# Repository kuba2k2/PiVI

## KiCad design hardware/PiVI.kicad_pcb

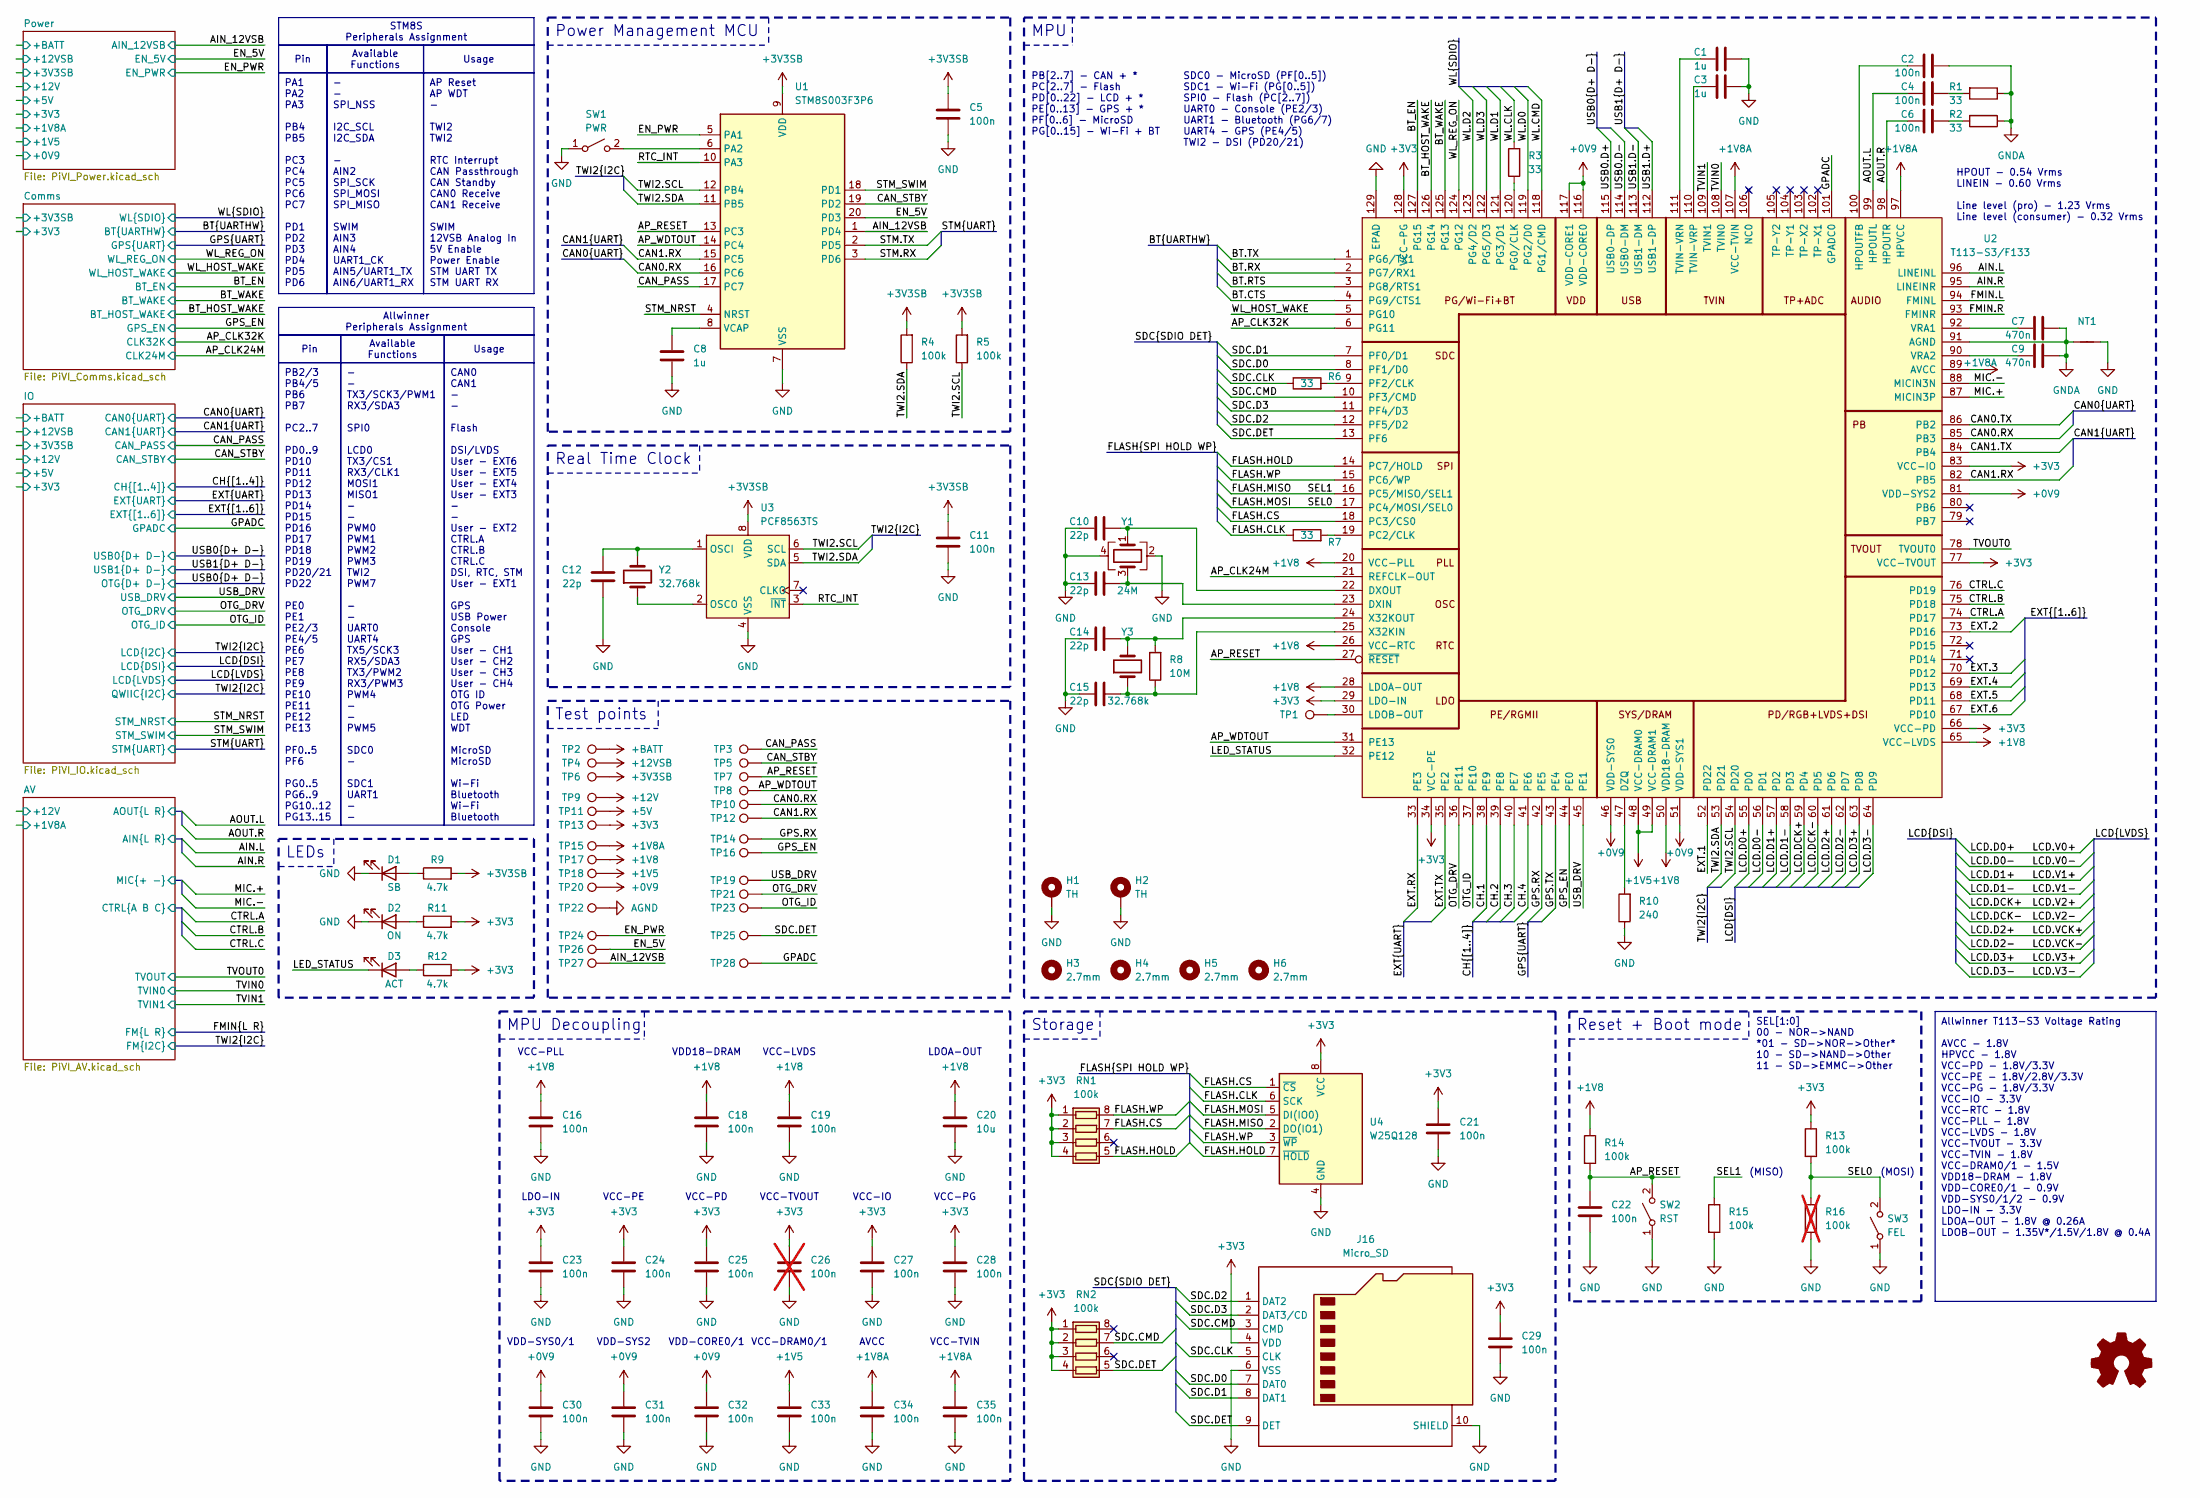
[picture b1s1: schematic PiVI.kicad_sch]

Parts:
C1, C3, C8: 1u; C_0603_1608Metric; MPN C29936
C2, C4, C5, C6, C11, C16, C18, C19, C21, C22, C23, C24, C25, C27, C28, C29, C30, C31, C32, C33, C34, C35: 100n; C_0603_1608Metric; MPN C14663
C7, C9: 470n; C_0603_1608Metric; MPN C1623
C10, C12, C13, C14, C15: 22p; C_0603_1608Metric; MPN C105620
C20: 10u; C_0603_1608Metric; MPN C19702
C26: 100n; C_0603_1608Metric; MPN C14663; not fitted
D1: SB; LED_0603_1608Metric; MPN C965800
D2: ON; LED_0603_1608Metric; MPN C965799
D3: ACT; LED_0603_1608Metric; MPN C965804
G1: Logo_Open_Hardware_Small; OSHW-Logo_7.5x8mm_SilkScreen; MPN N/A
H1, H2: TH; ThermalVia_1.5mm; MPN N/A
H3, H4, H5, H6: 2.7mm; MountingHole_2.7mm; MPN N/A
J16: Micro_SD; microSD_External_Pin; MPN C393941
NT1: NetTie-2_SMD_Pad0.5mm; MPN N/A
R1, R2, R3, R6, R7: 33; R_0603_1608Metric; MPN C2907154
R4, R5, R13, R14, R15: 100k; R_0603_1608Metric; MPN C2907088
R8: 10M; R_0603_1608Metric; MPN C2907090
R9, R11, R12: 4.7k; R_0603_1608Metric; MPN C2907166
R10: 240; R_0603_1608Metric; MPN C2907130
R16: 100k; R_0603_1608Metric; MPN C2907088; not fitted
RN1, RN2: 100k; R_Array_Convex_4x0603; MPN C173315
SW1: PWR; SW_SPST_B3U-1000P; MPN C455281
SW2: RST; SW_SPST_B3U-1000P; MPN C455281
SW3: FEL; SW_SPST_B3U-1000P; MPN C455281
TP1: LDOB-OUT; TestPoint-0.75mm; MPN N/A
TP2: +BATT; TestPoint-0.75mm; MPN N/A
TP3: CAN_PASS; TestPoint-0.75mm; MPN N/A
TP4: +12SB; TestPoint-0.75mm; MPN N/A
TP5: CAN_STBY; TestPoint-0.75mm; MPN N/A
TP6: +3V3SB; TestPoint-0.75mm; MPN N/A
TP7: AP_RESET; TestPoint-0.75mm; MPN N/A
TP8: AP_WDTOUT; TestPoint-0.75mm; MPN N/A
TP9: +12V; TestPoint-0.75mm; MPN N/A
TP10: CAN0.RX; TestPoint-0.75mm; MPN N/A
TP11: +5V; TestPoint-0.75mm; MPN N/A
TP12: CAN1.RX; TestPoint-0.75mm; MPN N/A
TP13: +3V3; TestPoint-0.75mm; MPN N/A
TP14: GPS.RX; TestPoint-0.75mm; MPN N/A
TP15: +1V8A; TestPoint-0.75mm; MPN N/A
TP16: GPS_EN; TestPoint-0.75mm; MPN N/A
TP17: +1V8; TestPoint-0.75mm; MPN N/A
TP18: +1V5; TestPoint-0.75mm; MPN N/A
TP19: USB_DRV; TestPoint-0.75mm; MPN N/A
TP20: +0V9; TestPoint-0.75mm; MPN N/A
TP21: OTG_DRV; TestPoint-0.75mm; MPN N/A
TP22: AGND; TestPoint-0.75mm; MPN N/A
TP23: OTG_ID; TestPoint-0.75mm; MPN N/A
TP24: EN_PWR; TestPoint-0.75mm; MPN N/A
TP25: SDC.DET; TestPoint-0.75mm; MPN N/A
TP26: EN_5V; TestPoint-0.75mm; MPN N/A
TP27: AIN_12SB; TestPoint-0.75mm; MPN N/A
TP28: GPADC; TestPoint-0.75mm; MPN N/A
U1: STM8S003F3P6; TSSOP-20_4.4x6.5mm_P0.65mm; MPN C52717
U2: T113-S3/F133; eLQFP-128_14x14mm_P0.4mm; MPN C5197687/C22438485
U3: PCF8563TS; MSOP-8_3x3mm_P0.65mm; MPN C269878
U4: W25Q128; SOIC-8_5.275x5.275mm_P1.27mm; MPN C97521
Y1: 24M; Crystal_SMD_3225-4Pin_3.2x2.5mm; MPN C70590
Y2, Y3: 32.768k; Crystal_SMD_3215-2Pin_3.2x1.5mm; MPN C5361379

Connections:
+0V9: C30.1, C31.1, C32.1, TP20.1, U2.46 (VDD-SYS0), U2.51 (VDD-SYS1), U2.81 (VDD-SYS2), U2.116 (VDD-CORE0), U2.117 (VDD-CORE1); also elsewhere on the board
+1V5: C33.1, TP18.1, U2.48 (VCC-DRAM0), U2.49 (VCC-DRAM1); also elsewhere on the board
+1V8: C16.1, C18.1, C19.1, C20.1, R14.1, TP17.1, U2.20 (VCC-PLL), U2.26 (VCC-RTC), U2.28 (LDOA-OUT), U2.50 (VDD18-DRAM), U2.65 (VCC-LVDS)
+1V8A: C34.1, C35.1, TP15.1, U2.89 (AVCC), U2.97 (HPVCC), U2.107 (VCC-TVIN); also elsewhere on the board
+3V3: C21.1, C23.1, C24.1, C25.1, C26.1, C27.1, C28.1, C29.1, J16.4 (VDD), R11.2, R12.2, R13.1, RN1.1 (R1.1), RN1.2 (R2.1), RN1.3 (R3.1), RN1.4 (R4.1), RN2.1 (R1.1), RN2.2 (R2.1), RN2.3 (R3.1), RN2.4 (R4.1), TP13.1, U2.29 (LDO-IN), U2.34 (VCC-PE), U2.66 (VCC-PD), U2.77 (VCC-TVOUT), U2.83 (VCC-IO), U2.128 (VCC-PG), U4.8 (VCC); also elsewhere on the board
+3V3SB: C5.1, C11.1, R4.2, R5.2, R9.2, TP6.1, U1.9 (VDD), U3.8 (VDD); also elsewhere on the board
+5V: TP11.1; also elsewhere on the board
+12V: TP9.1; also elsewhere on the board
+12VSB: TP4.1; also elsewhere on the board
+BATT: TP2.1; also elsewhere on the board
/AIN_12VSB: TP27.1, U1.1 (PD4); also elsewhere on the board
/AP_CLK24M: U2.21 (REFCLK-OUT); also elsewhere on the board
/AP_CLK32K: U2.6 (PG11); also elsewhere on the board
/AP_RESET: C22.2, R14.2, SW2.2 (B), TP7.1, U1.13 (PC3), U2.27 (~RESET)
/AP_WDTOUT: TP8.1, U1.14 (PC4), U2.31 (PE13)
/AV/AIN.L: U2.96 (LINEINL); also elsewhere on the board
/AV/AIN.R: U2.95 (LINEINR); also elsewhere on the board
/AV/AOUT.L: C4.2, U2.99 (HPOUTL); also elsewhere on the board
/AV/AOUT.R: C6.2, U2.98 (HPOUTR); also elsewhere on the board
/AV/CTRL.A: U2.74 (PD17); also elsewhere on the board
/AV/CTRL.B: U2.75 (PD18); also elsewhere on the board
/AV/CTRL.C: U2.76 (PD19); also elsewhere on the board
/AV/MIC.+: U2.87 (MICIN3P); also elsewhere on the board
/AV/MIC.-: U2.88 (MICIN3N); also elsewhere on the board
/BT.CTS: U2.4 (PG9/CTS1); also elsewhere on the board
/BT.RTS: U2.3 (PG8/RTS1); also elsewhere on the board
/BT.RX: U2.2 (PG7/RX1); also elsewhere on the board
/BT.TX: U2.1 (PG6/TX1); also elsewhere on the board
/BT_EN: U2.127 (PG15); also elsewhere on the board
/BT_HOST_WAKE: U2.126 (PG14); also elsewhere on the board
/BT_WAKE: U2.125 (PG13); also elsewhere on the board
/CAN0.RX: TP10.1, U1.16 (PC6), U2.85 (PB3); also elsewhere on the board
/CAN0.TX: U2.86 (PB2); also elsewhere on the board
/CAN1.RX: TP12.1, U1.15 (PC5), U2.82 (PB5); also elsewhere on the board
/CAN1.TX: U2.84 (PB4); also elsewhere on the board
/CAN_PASS: TP3.1, U1.17 (PC7); also elsewhere on the board
/CAN_STBY: TP5.1, U1.19 (PD2); also elsewhere on the board
/CH.1: U2.38 (PE9); also elsewhere on the board
/CH.2: U2.39 (PE8); also elsewhere on the board
/CH.3: U2.40 (PE7); also elsewhere on the board
/CH.4: U2.41 (PE6); also elsewhere on the board
/EN_5V: TP26.1, U1.20 (PD3); also elsewhere on the board
/EN_PWR: TP24.1, U1.5 (PA1); also elsewhere on the board
/EXT.1: U2.52 (PD22); also elsewhere on the board
/EXT.2: U2.73 (PD16); also elsewhere on the board
/EXT.3: U2.70 (PD12); also elsewhere on the board
/EXT.4: U2.69 (PD13); also elsewhere on the board
/EXT.5: U2.68 (PD11); also elsewhere on the board
/EXT.6: U2.67 (PD10); also elsewhere on the board
/EXT.RX: U2.33 (PE3); also elsewhere on the board
/EXT.TX: U2.35 (PE2); also elsewhere on the board
/FLASH.CLK: R7.1, U4.6 (SCK)
/FLASH.CS: RN1.7 (R2.2), U2.18 (PC3/CS0), U4.1 (~CS)
/FLASH.HOLD: RN1.5 (R4.2), U2.14 (PC7/HOLD), U4.7 (~HOLD)
/FLASH.MISO: R15.1, U2.16 (PC5/MISO/SEL1), U4.2 (DO(IO1))
/FLASH.MOSI: R13.2, R16.1, SW3.2 (B), U2.17 (PC4/MOSI/SEL0), U4.5 (DI(IO0))
/FLASH.WP: RN1.8 (R1.2), U2.15 (PC6/WP), U4.3 (~WP)
/FMIN.L: U2.94 (FMINL); also elsewhere on the board
/FMIN.R: U2.93 (FMINR); also elsewhere on the board
/GPADC: TP28.1, U2.101 (GPADC0)
/GPS.RX: TP14.1, U2.42 (PE5); also elsewhere on the board
/GPS.TX: U2.43 (PE4); also elsewhere on the board
/GPS_EN: TP16.1, U2.44 (PE0); also elsewhere on the board
/LCD.V0+: U2.55 (PD0); also elsewhere on the board
/LCD.V0-: U2.56 (PD1); also elsewhere on the board
/LCD.V1+: U2.57 (PD2); also elsewhere on the board
/LCD.V1-: U2.58 (PD3); also elsewhere on the board
/LCD.V2+: U2.59 (PD4); also elsewhere on the board
/LCD.V2-: U2.60 (PD5); also elsewhere on the board
/LCD.V3+: U2.63 (PD8); also elsewhere on the board
/LCD.V3-: U2.64 (PD9); also elsewhere on the board
/LCD.VCK+: U2.61 (PD6); also elsewhere on the board
/LCD.VCK-: U2.62 (PD7); also elsewhere on the board
/LED_STATUS: D3.1 (K), U2.32 (PE12)
/OTG_DRV: TP21.1, U2.36 (PE11); also elsewhere on the board
/OTG_ID: TP23.1, U2.37 (PE10); also elsewhere on the board
/RTC_INT: U1.10 (PA3), U3.3 (~INT)
/SDC.CLK: J16.5 (CLK), R6.1
/SDC.CMD: J16.3 (CMD), RN2.7 (R2.2), U2.10 (PF3/CMD)
/SDC.D0: J16.7 (DAT0), U2.8 (PF1/D0)
/SDC.D1: J16.8 (DAT1), U2.7 (PF0/D1)
/SDC.D2: J16.1 (DAT2), U2.12 (PF5/D2)
/SDC.D3: J16.2 (DAT3/CD), U2.11 (PF4/D3)
/SDC.DET: J16.9 (DET), RN2.5 (R4.2), TP25.1, U2.13 (PF6)
/STM.RX: U1.3 (PD6); also elsewhere on the board
/STM.TX: U1.2 (PD5); also elsewhere on the board
/STM_NRST: U1.4 (NRST); also elsewhere on the board
/STM_SWIM: U1.18 (PD1); also elsewhere on the board
/TVIN0: U2.108 (TVIN0); also elsewhere on the board
/TVIN1: U2.109 (TVIN1); also elsewhere on the board
/TVOUT0: U2.78 (TVOUT0); also elsewhere on the board
/USB1.D+: U2.112 (USB1-DP); also elsewhere on the board
/USB1.D-: U2.113 (USB1-DM); also elsewhere on the board
/USB_DRV: TP19.1, U2.45 (PE1); also elsewhere on the board
/WL.CLK: R3.2; also elsewhere on the board
/WL.CMD: U2.118 (PG1/CMD); also elsewhere on the board
/WL.D0: U2.119 (PG2/D0); also elsewhere on the board
/WL.D1: U2.121 (PG3/D1); also elsewhere on the board
/WL.D2: U2.123 (PG4/D2); also elsewhere on the board
/WL.D3: U2.122 (PG5/D3); also elsewhere on the board
/WL_HOST_WAKE: U2.5 (PG10); also elsewhere on the board
/WL_REG_ON: U2.124 (PG12); also elsewhere on the board
AGND: TP22.1; also elsewhere on the board
GND: C1.1, C3.1, C5.2, C8.1, C10.1, C11.2, C12.1, C13.1, C14.1, C15.1, C16.2, C18.2, C19.2, C20.2, C21.2, C22.1, C23.2, C24.2, C25.2, C26.2, C27.2, C28.2, C29.2, C30.2, C31.2, C32.2, C33.2, C34.2, C35.2, D1.1 (K), D2.1 (K), H1.1, H2.1, J16.6 (VSS), J16.10 (SHIELD), NT1.2, R10.1, R15.2, R16.2, SW1.1 (A), SW2.1 (A), SW3.1 (A), U1.7 (VSS), U2.129 (EPAD), U3.4 (VSS), U4.4 (GND), Y1.2, Y1.4; also elsewhere on the board
GNDA: C2.1, C7.2, C9.2, NT1.1, R1.1, R2.1, U2.91 (AGND); also elsewhere on the board
unnamed: C4.1, R1.2
unnamed: C6.1, R2.2
unnamed: D1.2 (A), R9.1
unnamed: D2.2 (A), R11.1
unnamed: D3.2 (A), R12.1
unnamed: SW1.2 (B), U1.6 (PA2)
unnamed: C8.2, U1.8 (VCAP)
unnamed: C13.2, U2.23 (DXIN), Y1.3
unnamed: C10.2, U2.22 (DXOUT), Y1.1
unnamed: R10.2, U2.47 (DZQ)
unnamed: C2.2, U2.100 (HPOUTFB)
unnamed: TP1.1, U2.30 (LDOB-OUT)
unnamed: R7.2, U2.19 (PC2/CLK)
unnamed: R6.2, U2.9 (PF2/CLK)
unnamed: R3.1, U2.120 (PG0/CLK)
unnamed: C1.2, U2.111 (TVIN-VRN)
unnamed: C3.2, U2.110 (TVIN-VRP)
unnamed: C7.1, U2.92 (VRA1)
unnamed: C9.1, U2.90 (VRA2)
unnamed: C15.2, R8.1, U2.25 (X32KIN), Y3.1
unnamed: C14.2, R8.2, U2.24 (X32KOUT), Y3.2
unnamed: C12.2, U3.1 (OSCI), Y2.2
unnamed: U3.2 (OSCO), Y2.1

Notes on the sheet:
Pin
Usage
- - TX3/SCK3/PWM1 RX3/SDA3 SPI0 LCD0 TX3/CS1 RX3/CLK1 MOSI1 MISO1 - - PWM0 PWM1 PWM2 PWM3 TWI2 PWM7 - - UART0 UART4 TX5/SCK3 RX5/SDA3 TX3/PWM2 RX3/PWM3 PWM4 - - PWM5 SDC0 - SDC1 UART1 - -
AP Reset AP WDT - TWI2 TWI2 RTC Interrupt CAN Passthrough CAN Standby CAN0 Receive CAN1 Receive SWIM 12VSB Analog In 5V Enable Power Enable STM UART TX STM UART RX
- - SPI_NSS I2C_SCL I2C_SDA - AIN2 SPI_SCK SPI_MOSI SPI_MISO SWIM AIN3 AIN4 UART1_CK AIN5/UART1_TX AIN6/UART1_RX
Allwinner T113-S3 Voltage Rating AVCC - 1.8V HPVCC - 1.8V VCC-PD - 1.8V/3.3V VCC-PE - 1.8V/2.8V/3.3V VCC-PG - 1.8V/3.3V VCC-IO - 3.3V VCC-RTC - 1.8V VCC-PLL - 1.8V VCC-LVDS - 1.8V VCC-TVOUT - 3.3V VCC-TVIN - 1.8V VCC-DRAM0/1 - 1.5V VDD18-DRAM - 1.8V VDD-CORE0/1 - 0.9V VDD-SYS0/1/2 - 0.9V LDO-IN - 3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
Available Functions
PA1 PA2 PA3 PB4 PB5 PC3 PC4 PC5 PC6 PC7 PD1 PD2 PD3 PD4 PD5 PD6
PB2/3 PB4/5 PB6 PB7 PC2..7 PD0..9 PD10 PD11 PD12 PD13 PD14 PD15 PD16 PD17 PD18 PD19 PD20/21 PD22 PE0 PE1 PE2/3 PE4/5 PE6 PE7 PE8 PE9 PE10 PE11 PE12 PE13 PF0..5 PF6 PG0..5 PG6..9 PG10..12 PG13..15
CAN0 CAN1 - - Flash DSI/LVDS User - EXT6 User - EXT5 User - EXT4 User - EXT3 - - User - EXT2 CTRL.A CTRL.B CTRL.C DSI, RTC, STM User - EXT1 GPS USB Power Console GPS User - CH1 User - CH2 User - CH3 User - CH4 OTG ID OTG Power LED WDT MicroSD MicroSD Wi-Fi Bluetooth Wi-Fi Bluetooth
STM8S Peripherals Assignment
Allwinner Peripherals Assignment
(MOSI)
SDC0 - MicroSD (PF[0..5]) SDC1 - Wi-Fi (PG[0..5]) SPI0 - Flash (PC[2..7]) UART0 - Console (PE2/3) UART1 - Bluetooth (PG6/7) UART4 - GPS (PE4/5) TWI2 - DSI (PD20/21)
VCC-DRAM0/1
VDD-SYS2
VCC-PE
VCC-PD
LDO-IN
HPOUT - 0.54 Vrms LINEIN - 0.60 Vrms Line level (pro) - 1.23 Vrms Line level (consumer) - 0.32 Vrms
Power Management MCU
SEL[1:0] 00 - NOR->NAND *01 - SD->NOR->Other* 10 - SD->NAND->Other 11 - SD->EMMC->Other
VCC-IO
Storage
VDD-SYS0/1
LEDs
Reset + Boot mode
Real Time Clock
VDD-CORE0/1
VCC-PLL
VCC-TVOUT
VCC-PG
PB[2..7] - CAN + * PC[2..7] - Flash PD[0..22] - LCD + * PE[0..13] - GPS + * PF[0..6] - MicroSD PG[0..15] - Wi-Fi + BT
(MISO)
MPU Decoupling
VCC-LVDS
LDOA-OUT
VCC-TVIN
MPU
Test points

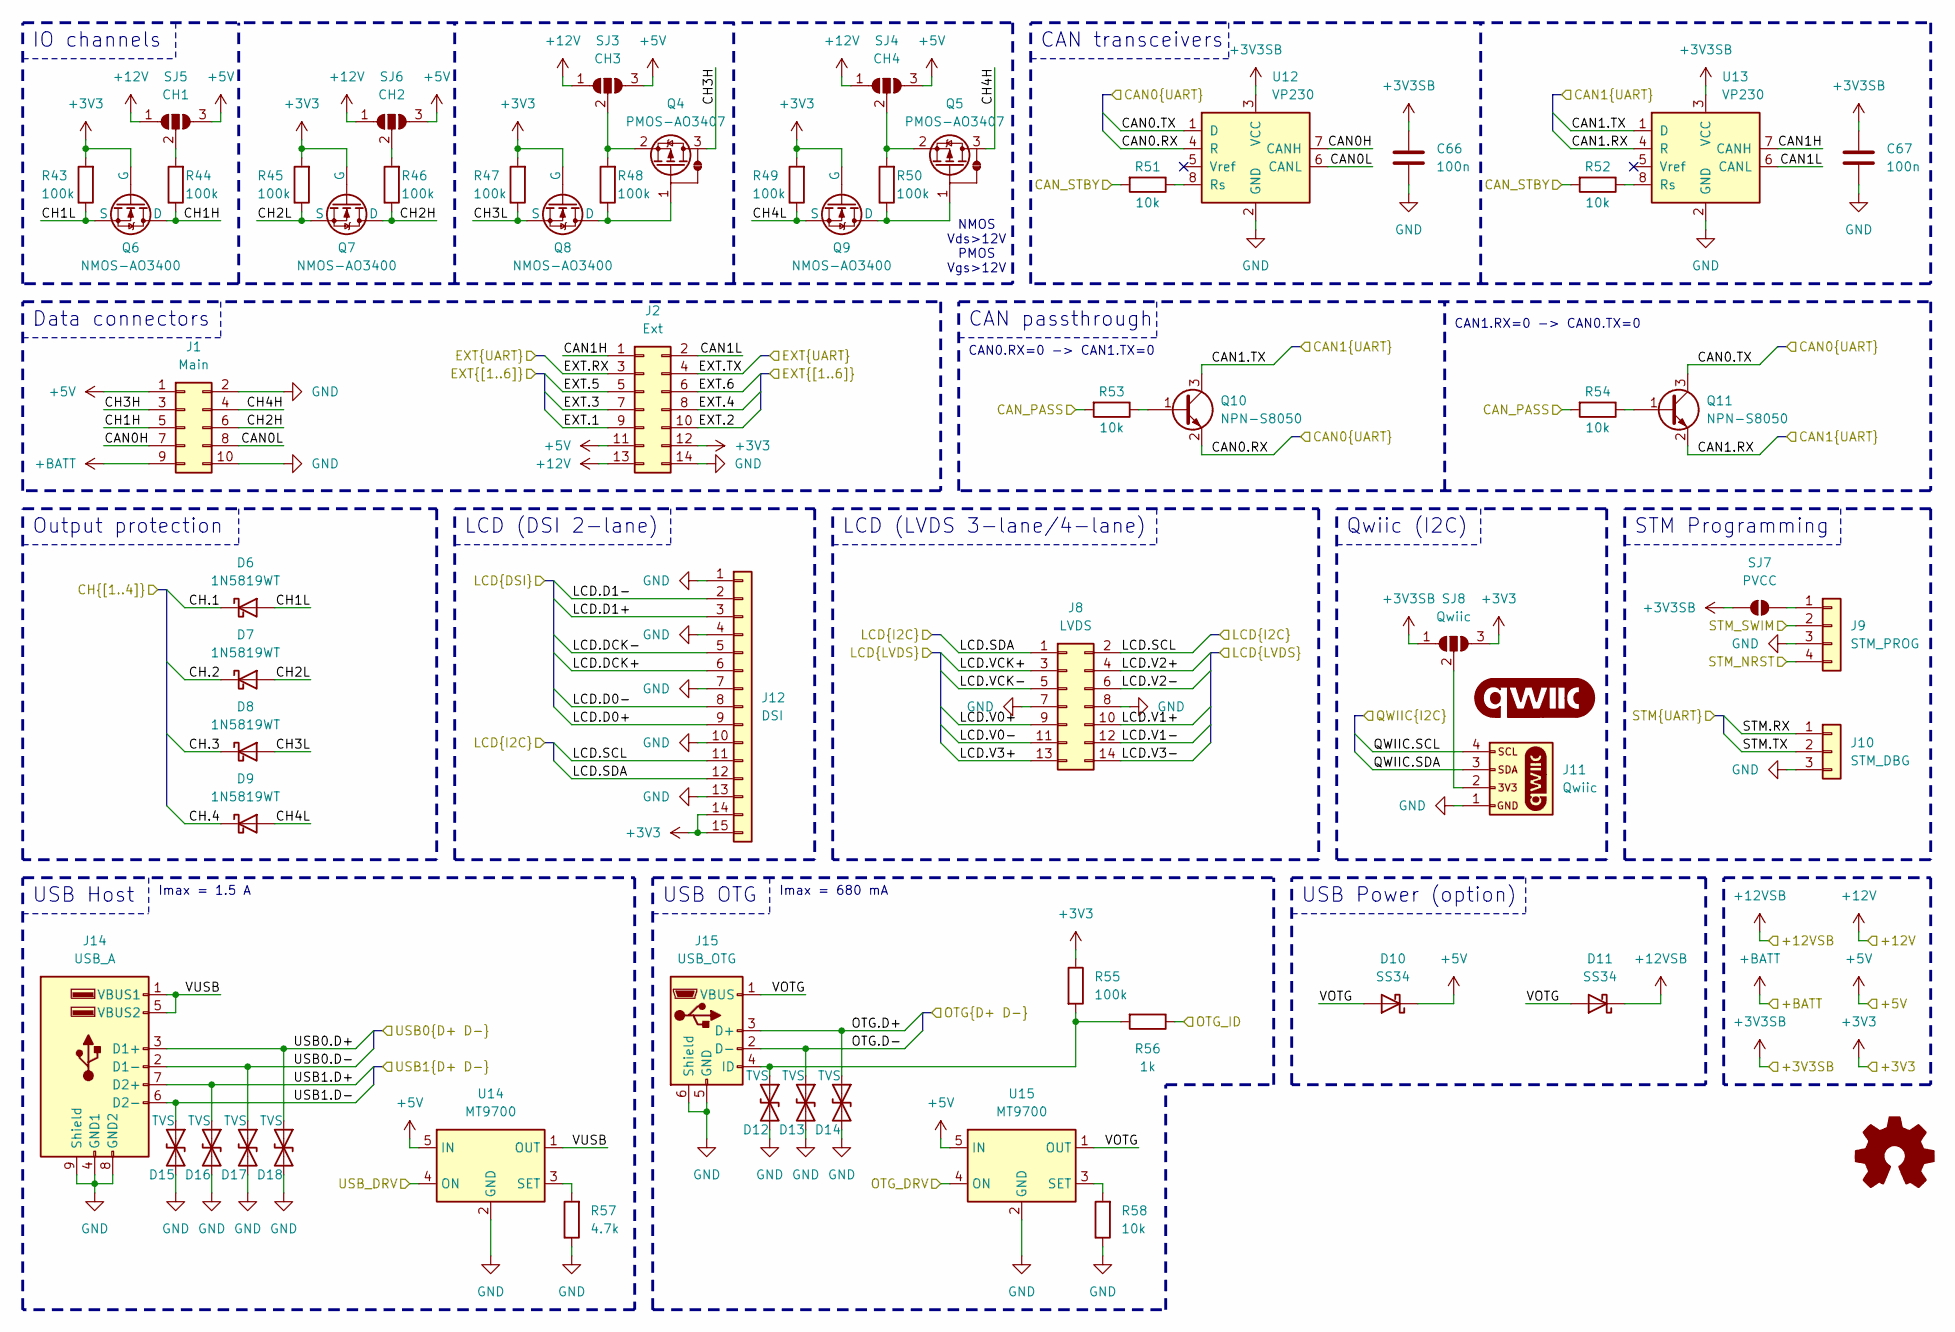
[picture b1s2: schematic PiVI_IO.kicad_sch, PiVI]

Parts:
C66, C67: 100n; C_0603_1608Metric; MPN C14663
D6, D7, D8, D9: 1N5819WT; D_SOD-523; MPN C5451630
D10, D11: SS34; D_SMA; MPN C2836396
D12, D13, D14, D15, D16, D17, D18: TVS; D_SOD-523; MPN C3008120
G2: qwiic_Logo; qwiic_5.5mm; MPN N/A
J1: Main; PinHeader_2x05_P2.54mm_Vertical; MPN C19190512/C19190511
J2: Ext; PinHeader_2x07_P2.54mm_Vertical; MPN C19190512/C19190511
J8: LVDS; PinHeader_2x07_P2.54mm_Vertical; MPN C19190512/C19190511
J9: STM_PROG; PinHeader_1x04_P2.54mm_Vertical; MPN C2337
J10: STM_DBG; PinHeader_1x03_P2.54mm_Vertical; MPN C2337
J11: Qwiic; JST_SMD_1.0mm-4_Vertical; MPN C160390
J12: DSI; TE-1-1734248-5; MPN C2922285
J14: USB_A; USB_A_CUI_UJ2-ADH-TH_Horizontal_Stacked; MPN C456021
J15: USB_OTG; USB_Micro-B_MicroXNJ; MPN C404969
Q4, Q5: PMOS-AO3407; SOT-23-GDPASS; MPN C347478
Q6, Q7, Q8, Q9: NMOS-AO3400; SOT-23; MPN C20628874
Q10, Q11: NPN-S8050; SOT-23; MPN C181158
R43, R44, R45, R46, R47, R48, R49, R50, R55: 100k; R_0603_1608Metric; MPN C2907088
R51, R52, R53, R54, R58: 10k; R_0603_1608Metric; MPN C2930027
R56: 1k; R_0603_1608Metric; MPN C2907113
R57: 4.7k; R_0603_1608Metric; MPN C2907166
SJ3: CH3; Jumper_3_NO; MPN N/A
SJ4: CH4; Jumper_3_NO; MPN N/A
SJ5: CH1; Jumper_3_NO; MPN N/A
SJ6: CH2; Jumper_3_NO; MPN N/A
SJ7: PVCC; Jumper_2_NO; MPN N/A
SJ8: Qwiic; Jumper_3_NO; MPN N/A
U12, U13: VP230; SOIC-8_3.9x4.9mm_P1.27mm; MPN C12084
U14, U15: MT9700; SOT-23-5; MPN C89855

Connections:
+3V3: J2.12, J12.14, J12.15, Q6.1 (G), Q7.1 (G), Q8.1 (G), Q9.1 (G), R43.2, R45.2, R47.2, R49.2, R55.1, SJ8.3 (B); also elsewhere on the board
+3V3SB: C66.1, C67.1, SJ7.1 (A), SJ8.1 (A), U12.3 (VCC), U13.3 (VCC); also elsewhere on the board
+5V: D10.1 (K), J1.1, J2.11, SJ3.3 (B), SJ4.3 (B), SJ5.3 (B), SJ6.3 (B), U14.5 (IN), U15.5 (IN); also elsewhere on the board
+12V: J2.13, SJ3.1 (A), SJ4.1 (A), SJ5.1 (A), SJ6.1 (A); also elsewhere on the board
+12VSB: D11.1 (K); also elsewhere on the board
+BATT: J1.9; also elsewhere on the board
/CAN0.RX: Q10.2 (E), U12.4 (R); also elsewhere on the board
/CAN0.TX: Q11.3 (C), U12.1 (D); also elsewhere on the board
/CAN1.RX: Q11.2 (E), U13.4 (R); also elsewhere on the board
/CAN1.TX: Q10.3 (C), U13.1 (D); also elsewhere on the board
/CAN_PASS: R53.2, R54.2; also elsewhere on the board
/CAN_STBY: R51.2, R52.2; also elsewhere on the board
/CH.1: D6.1 (K); also elsewhere on the board
/CH.2: D7.1 (K); also elsewhere on the board
/CH.3: D8.1 (K); also elsewhere on the board
/CH.4: D9.1 (K); also elsewhere on the board
/EXT.1: J2.9; also elsewhere on the board
/EXT.2: J2.10; also elsewhere on the board
/EXT.3: J2.7; also elsewhere on the board
/EXT.4: J2.8; also elsewhere on the board
/EXT.5: J2.5; also elsewhere on the board
/EXT.6: J2.6; also elsewhere on the board
/EXT.RX: J2.3; also elsewhere on the board
/EXT.TX: J2.4; also elsewhere on the board
/IO/CAN0H: J1.7, U12.7 (CANH)
/IO/CAN0L: J1.8, U12.6 (CANL)
/IO/CAN1H: J2.1, U13.7 (CANH)
/IO/CAN1L: J2.2, U13.6 (CANL)
/IO/CH1H: J1.5, Q6.3 (D), R44.1
/IO/CH1L: D6.2 (A), Q6.2 (S), R43.1
/IO/CH2H: J1.6, Q7.3 (D), R46.1
/IO/CH2L: D7.2 (A), Q7.2 (S), R45.1
/IO/CH3H: J1.3, Q4.3 (D)
/IO/CH3L: D8.2 (A), Q8.2 (S), R47.1
/IO/CH4H: J1.4, Q5.3 (D)
/IO/CH4L: D9.2 (A), Q9.2 (S), R49.1
/IO/VOTG: D10.2 (A), D11.2 (A), J15.1 (VBUS), U15.1 (OUT)
/IO/VUSB: J14.1 (VBUS1), J14.5 (VBUS2), U14.1 (OUT)
/LCD.V0+: J8.9, J12.9; also elsewhere on the board
/LCD.V0-: J8.11, J12.8; also elsewhere on the board
/LCD.V1+: J8.10, J12.3; also elsewhere on the board
/LCD.V1-: J8.12, J12.2; also elsewhere on the board
/LCD.V2+: J8.4, J12.6; also elsewhere on the board
/LCD.V2-: J8.6, J12.5; also elsewhere on the board
/LCD.V3+: J8.13; also elsewhere on the board
/LCD.V3-: J8.14; also elsewhere on the board
/LCD.VCK+: J8.3; also elsewhere on the board
/LCD.VCK-: J8.5; also elsewhere on the board
/OTG_DRV: U15.4 (ON); also elsewhere on the board
/OTG_ID: R56.1; also elsewhere on the board
/STM.RX: J10.1; also elsewhere on the board
/STM.TX: J10.2; also elsewhere on the board
/STM_NRST: J9.4; also elsewhere on the board
/STM_SWIM: J9.2; also elsewhere on the board
/USB1.D+: D16.1 (A1), J14.7 (D2+); also elsewhere on the board
/USB1.D-: D15.1 (A1), J14.6 (D2-); also elsewhere on the board
/USB_DRV: U14.4 (ON); also elsewhere on the board
GND: C66.2, C67.2, D12.2 (A2), D13.2 (A2), D14.2 (A2), D15.2 (A2), D16.2 (A2), D17.2 (A2), D18.2 (A2), J1.2, J1.10, J2.14, J8.7, J8.8, J9.3, J10.3, J11.1, J12.1, J12.4, J12.7, J12.10, J12.13, J14.4 (GND1), J14.8 (GND2), J14.9 (Shield), J15.5 (GND), J15.6 (Shield), R57.1, R58.1, U12.2 (GND), U13.2 (GND), U14.2 (GND), U15.2 (GND); also elsewhere on the board
unnamed: D12.1 (A1), J15.4 (ID), R55.2, R56.2
unnamed: J9.1, SJ7.2 (B)
unnamed: J11.2, SJ8.2 (C)
unnamed: Q4.1 (G), Q8.3 (D), R48.1
unnamed: Q4.2 (S), R48.2, SJ3.2 (C)
unnamed: Q5.1 (G), Q9.3 (D), R50.1
unnamed: Q5.2 (S), R50.2, SJ4.2 (C)
unnamed: Q10.1 (B), R53.1
unnamed: Q11.1 (B), R54.1
unnamed: R44.2, SJ5.2 (C)
unnamed: R46.2, SJ6.2 (C)
unnamed: R51.1, U12.8 (Rs)
unnamed: R52.1, U13.8 (Rs)
unnamed: R57.2, U14.3 (SET)
unnamed: R58.2, U15.3 (SET)

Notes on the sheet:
USB Host
Imax = 680 mA
LCD (LVDS 3-lane/4-lane)
CAN transceivers
Data connectors
USB OTG
CAN1.RX=0 -> CAN0.TX=0
Imax = 1.5 A
LCD (DSI 2-lane)
STM Programming
Output protection
IO channels
NMOS Vds>12V PMOS Vgs>12V
CAN passthrough
Qwiic (I2C)
CAN0.RX=0 -> CAN1.TX=0
USB Power (option)

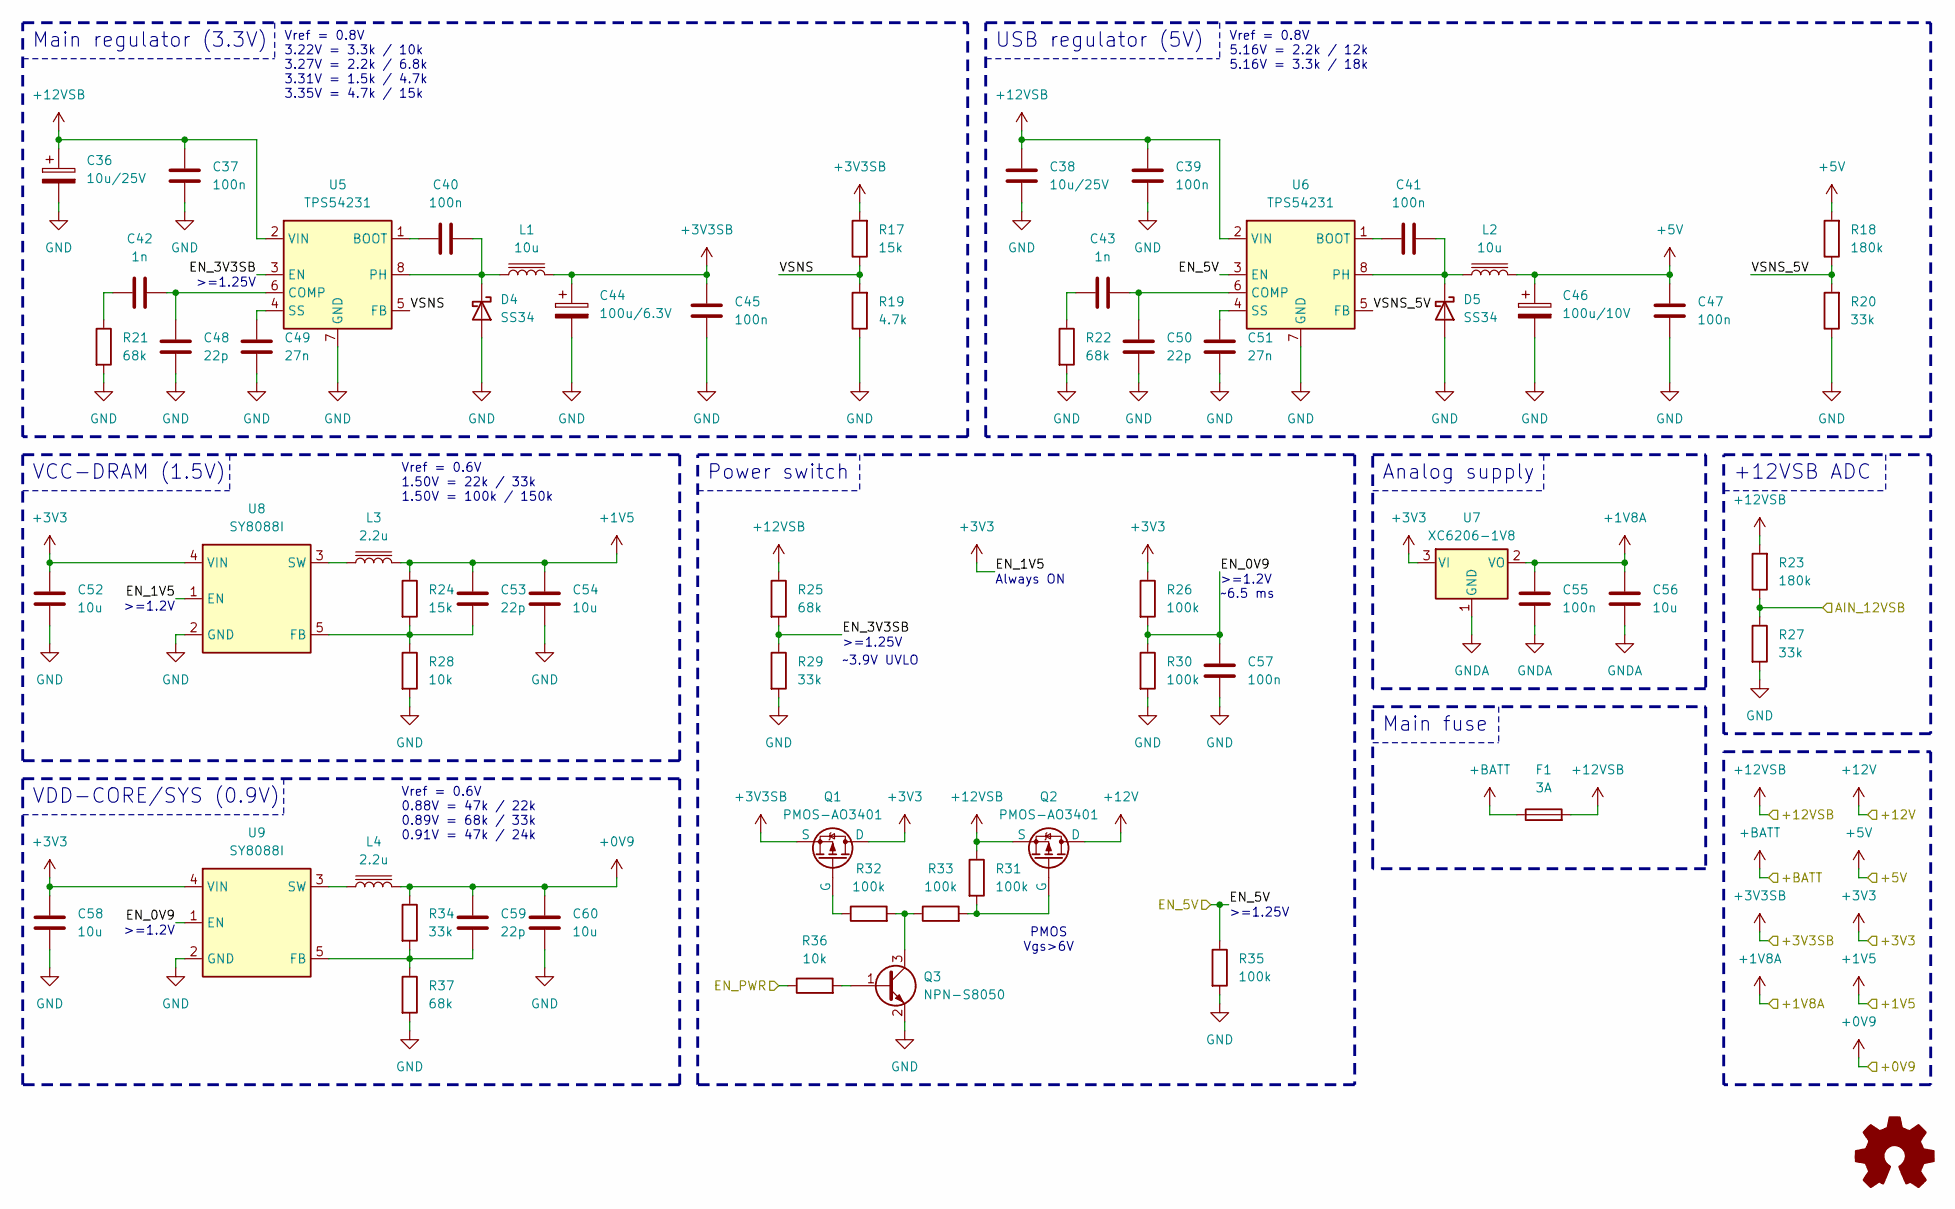
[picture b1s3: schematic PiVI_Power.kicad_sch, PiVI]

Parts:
C36: 10u/25V; CP_EIA-3528-21_Kemet-B; MPN C119050
C37, C39, C40, C41, C45, C47, C55, C57: 100n; C_0603_1608Metric; MPN C14663
C38: 10u/25V; C_0805_2012Metric; MPN C15850
C42, C43: 1n; C_0603_1608Metric; MPN C100040
C44: 100u/6.3V; CP_EIA-3528-21_Kemet-B; MPN C129289
C46: 100u/10V; CP_EIA-3528-21_Kemet-B; MPN C129567
C48, C50, C53, C59: 22p; C_0603_1608Metric; MPN C105620
C49, C51: 27n; C_0603_1608Metric; MPN C107086
C52, C54, C56, C58, C60: 10u; C_0603_1608Metric; MPN C19702
D4, D5: SS34; D_SMA; MPN C2836396
F1: 3A; Fuse_1206_3216Metric; MPN C14165
L1, L2: 10u; L_Changjiang_FNR4020S; MPN C602032
L3, L4: 2.2u; L_Sunlord_SWPA3015S; MPN C43389
Q1, Q2: PMOS-AO3401; SOT-23; MPN C20628875
Q3: NPN-S8050; SOT-23; MPN C181158
R17, R24: 15k; R_0603_1608Metric; MPN C2907104
R18, R23: 180k; R_0603_1608Metric; MPN C2907109
R19: 4.7k; R_0603_1608Metric; MPN C2907166
R20, R27, R29, R34: 33k; R_0603_1608Metric; MPN C2907153
R21, R22, R25, R37: 68k; R_0603_1608Metric; MPN C2907196
R26, R30, R31, R32, R33, R35: 100k; R_0603_1608Metric; MPN C2907088
R28, R36: 10k; R_0603_1608Metric; MPN C2930027
U5, U6: TPS54231; SOIC-8_3.9x4.9mm_P1.27mm; MPN C28023
U7: XC6206-1V8; SOT-23-3; MPN C5252894
U8, U9: SY8088I; TSOT-23-5; MPN C479072

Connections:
+0V9: C59.1, C60.1, L4.2, R34.1; also elsewhere on the board
+1V5: C53.1, C54.1, L3.2, R24.1; also elsewhere on the board
+1V8A: C55.1, C56.1, U7.2 (VO); also elsewhere on the board
+3V3: C52.1, C58.1, Q1.3 (D), R26.1, U7.3 (VI), U8.1 (EN), U8.4 (VIN), U9.4 (VIN); also elsewhere on the board
+3V3SB: C44.1, C45.1, L1.2, Q1.2 (S), R17.2; also elsewhere on the board
+5V: C46.1, C47.1, L2.2, R18.2; also elsewhere on the board
+12V: Q2.3 (D); also elsewhere on the board
+12VSB: C36.1, C37.1, C38.1, C39.1, F1.2, Q2.2 (S), R23.2, R25.1, R31.1, U5.2 (VIN), U6.2 (VIN); also elsewhere on the board
+BATT: F1.1; also elsewhere on the board
/AIN_12VSB: R23.1, R27.1; also elsewhere on the board
/EN_5V: R35.1, U6.3 (EN); also elsewhere on the board
/EN_PWR: R36.1; also elsewhere on the board
/Power/EN_0V9: C57.1, R26.2, R30.1, U9.1 (EN)
/Power/EN_3V3SB: R25.2, R29.1, U5.3 (EN)
/Power/VSNS: R17.1, R19.2, U5.5 (FB)
/Power/VSNS_5V: R18.1, R20.2, U6.5 (FB)
GND: C36.2, C37.2, C38.2, C39.2, C44.2, C45.2, C46.2, C47.2, C48.2, C49.2, C50.2, C51.2, C52.2, C54.2, C57.2, C58.2, C60.2, D4.2 (A), D5.2 (A), Q3.2 (E), R19.1, R20.1, R21.2, R22.2, R27.2, R28.2, R29.2, R30.2, R35.2, R37.2, U5.7 (GND), U6.7 (GND), U8.2 (GND), U9.2 (GND); also elsewhere on the board
GNDA: C55.2, C56.2, U7.1 (GND); also elsewhere on the board
unnamed: C42.2, R21.1
unnamed: C43.2, R22.1
unnamed: C40.2, D4.1 (K), L1.1, U5.8 (PH)
unnamed: C41.2, D5.1 (K), L2.1, U6.8 (PH)
unnamed: Q1.1 (G), R32.1
unnamed: Q2.1 (G), R31.2, R33.2
unnamed: Q3.1 (B), R36.2
unnamed: Q3.3 (C), R32.2, R33.1
unnamed: C40.1, U5.1 (BOOT)
unnamed: C42.1, C48.1, U5.6 (COMP)
unnamed: C49.1, U5.4 (SS)
unnamed: C41.1, U6.1 (BOOT)
unnamed: C43.1, C50.1, U6.6 (COMP)
unnamed: C51.1, U6.4 (SS)
unnamed: C53.2, R24.2, R28.1, U8.5 (FB)
unnamed: L3.1, U8.3 (SW)
unnamed: C59.2, R34.2, R37.1, U9.5 (FB)
unnamed: L4.1, U9.3 (SW)

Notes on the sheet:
>=1.2V
Analog supply
USB regulator (5V)
Main regulator (3.3V)
>=1.25V
VDD-CORE/SYS (0.9V)
VCC-DRAM (1.5V)
~3.9V UVLO
PMOS Vgs>6V
Main fuse
Vref = 0.8V 5.16V = 2.2k / 12k 5.16V = 3.3k / 18k
Power switch
Always ON
Vref = 0.6V 1.50V = 22k / 33k 1.50V = 100k / 150k
Vref = 0.8V 3.22V = 3.3k / 10k 3.27V = 2.2k / 6.8k 3.31V = 1.5k / 4.7k 3.35V = 4.7k / 15k
~6.5 ms
+12VSB ADC
Vref = 0.6V 0.88V = 47k / 22k 0.89V = 68k / 33k 0.91V = 47k / 24k

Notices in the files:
hardware/PiVI.kicad_pcb:
© kuba2k2
